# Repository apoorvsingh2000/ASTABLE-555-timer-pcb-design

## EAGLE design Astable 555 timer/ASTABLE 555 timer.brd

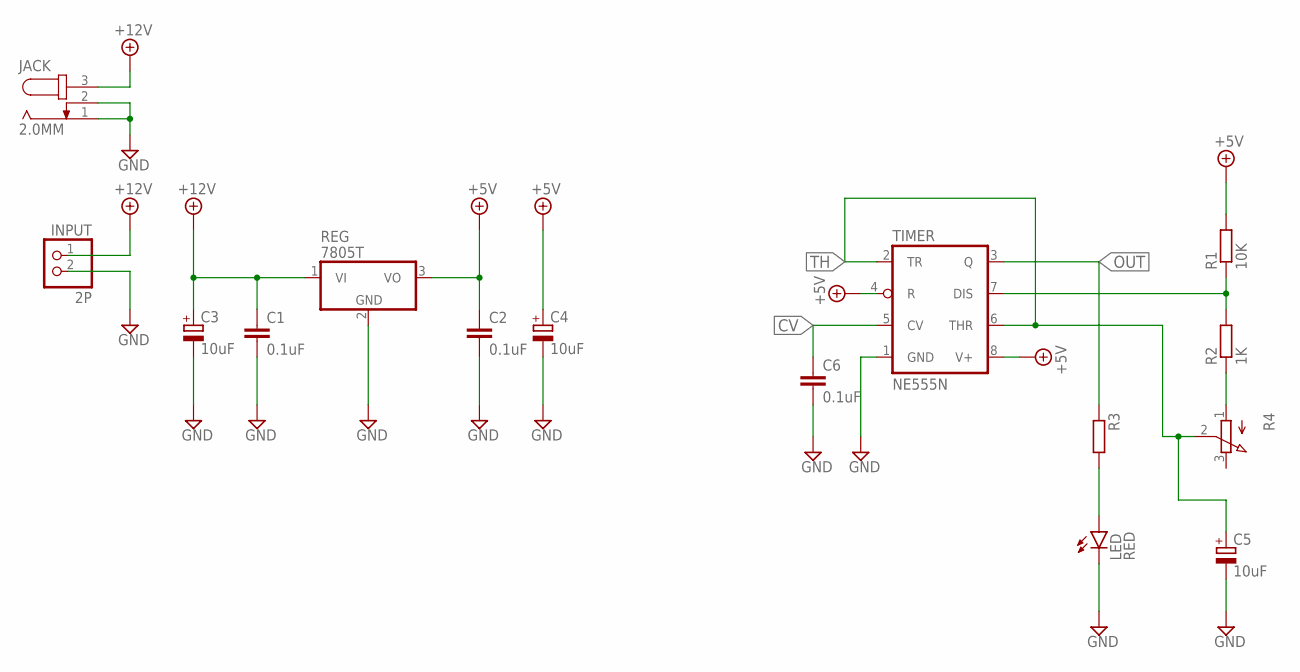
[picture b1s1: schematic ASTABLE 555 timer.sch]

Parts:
C1, C2, C6: 0.1uF; C050-030X075
C3, C4, C5: 10uF; E3,5-8
INPUT: 2P; 1X02
JACK: 2.0MM; SPC4078
LED: RED; LED5MM
R1: 10K; 0207/10
R2: 1K; 0207/10
R3: R-EU_0207/10; 0207/10
R4: 3RP/1610N
REG: 7805T; TO220H
TIMER: NE555N; DIL08

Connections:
+5V: C2.1, C4.+, R1.2, REG.3 (VO), TIMER.4 (R), TIMER.8 (V+)
+12V: C1.1, C3.+, INPUT.1, JACK.3, REG.1 (VI)
CV: C6.1, TIMER.5 (CV)
GND: C1.2, C2.2, C3.-, C4.-, C5.-, C6.2, INPUT.2, JACK.1, JACK.2, LED.K (C), REG.2 (GND), TIMER.1 (GND)
unnamed: R1.1, R2.2, TIMER.7 (DIS)
unnamed: R2.1, R4.1 (A)
unnamed: LED.A, R3.2
OUT: R3.1, TIMER.3 (Q)
TH: C5.+, R4.2 (S), TIMER.2 (TR), TIMER.6 (THR)

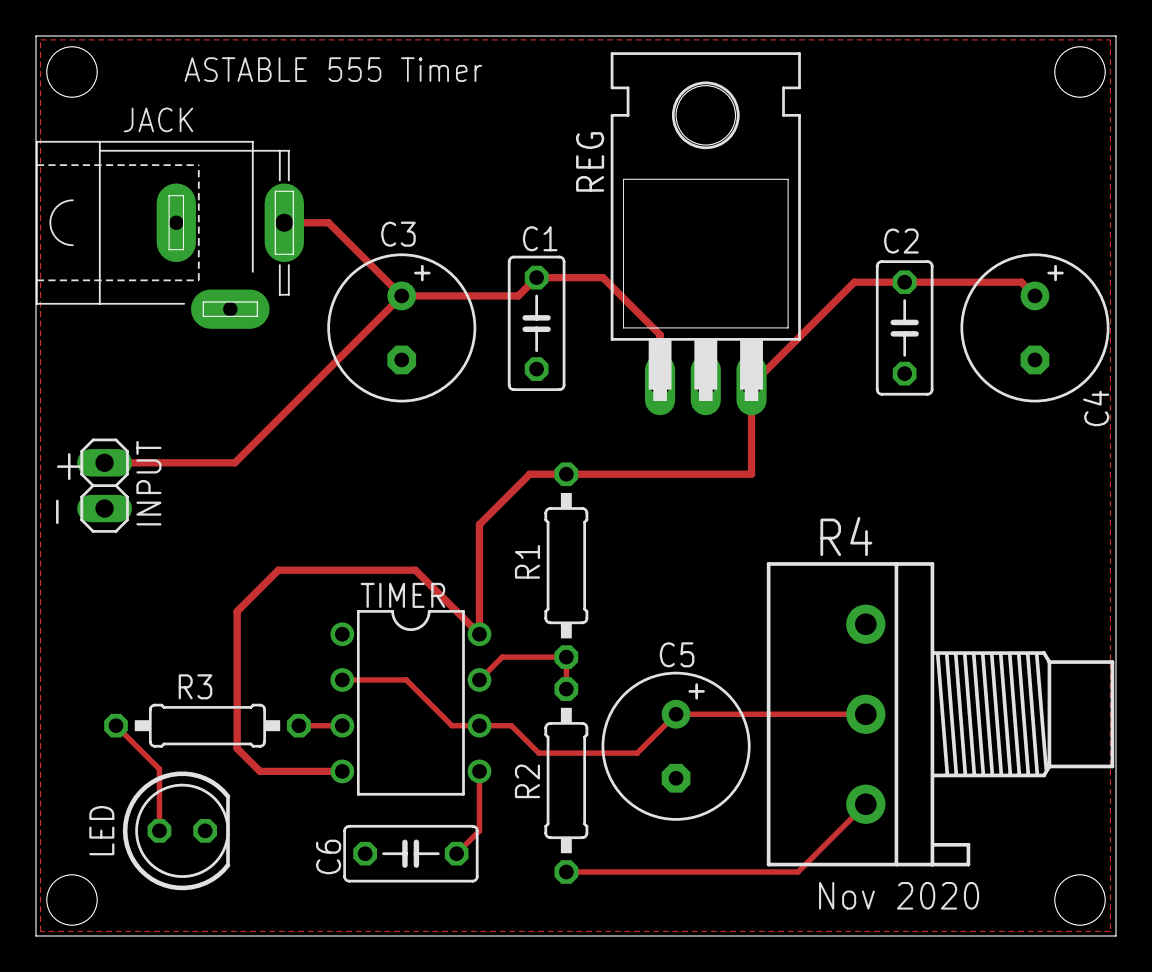
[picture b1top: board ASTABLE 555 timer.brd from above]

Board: 2 copper layers, 60.0 x 50.0 mm, 15 parts (0 on the bottom side), 9 nets.

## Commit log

2020-11-16 astable 555 timer
